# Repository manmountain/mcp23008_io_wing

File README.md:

# MCP23008 io-wing

* IO expander wing for Adafruit Feather boards

Missing IO pins in your feather project? The MCP23008 I2C GPIO expander is great for situations like this. Add another 8 pins to your Feather using a MCP23008 port expander. The MCP23008 uses two i2c pins (these can be shared with other i2c devices), and in exchange gives you 8 general purpose pins. You can set each of 8 pins to be input, output, or input with a pullup. There's even the ability to get an interrupt via an external pin when any of the inputs change so you don't have to keep polling the chip.

You can sink/source up to 20mA from any of the I/O pins so this will work for LEDs and such. You can set the i2c address by tying the ADDR0-2 pins to power or ground by shorting solder jumpers, for up to 8 unique addresses. That means 8 chips can share a single i2c bus - that's 64 I/O pins for your Feather!

## Configure i2c address

This wing uses i2c 7-bit address between 0x20-0x27, selectable with jumpers. On the left side of the wing there is 3 small solder jumpers labeled A0 - A2. By shorting out the solder jumper A0, A1, and A2 you can change the i2c address of the MCP23008.

| A2 | A1 | A0 | Address |
| --- | --- | --- | --- | 
| open | open | open | 0x20 |
| open | open | closed  | 0x21 |
| open | closed | open | 0x22 |
| open | closed | closed | 0x23 |
| closed | open | open | 0x24 |
| closed | open | closed  | 0x25 |
| closed | closed | open | 0x26 |
| closed | closed | closed | 0x27 |

## Using interrupts

To use the interrupt from the MCP23008 short one of the solder jumper on the backside of the wing to connect the interrupt pin from the MCP23008 to the corresponding pin on the Feather.

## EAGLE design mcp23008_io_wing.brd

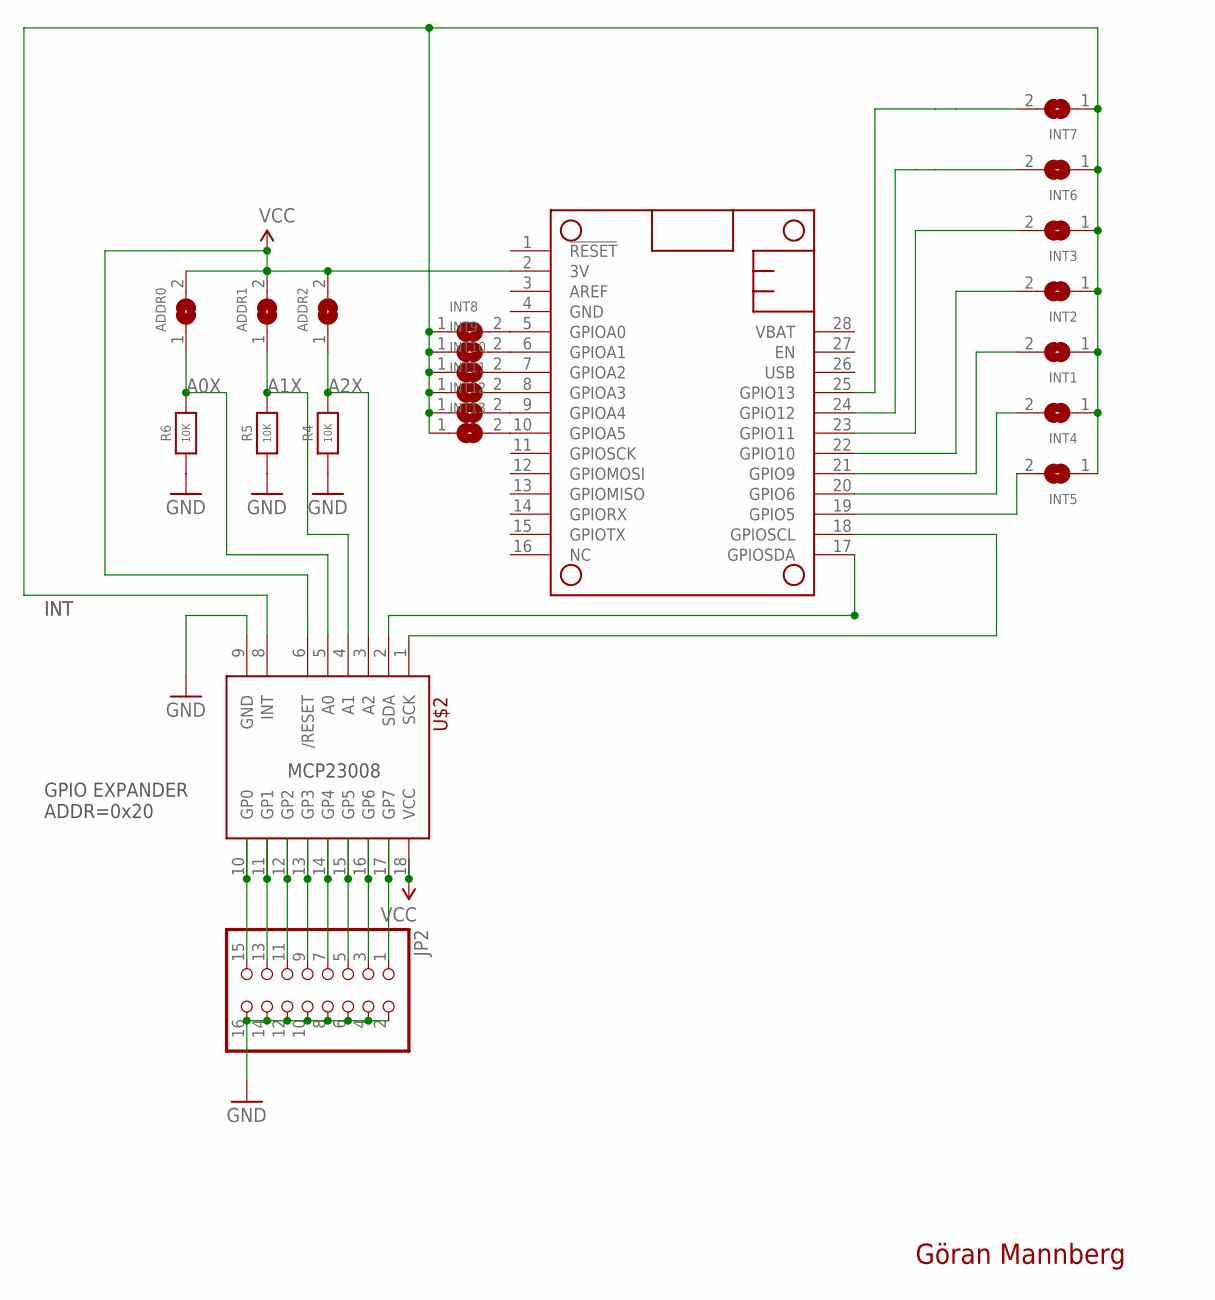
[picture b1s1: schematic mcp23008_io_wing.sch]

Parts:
ADDR0, ADDR1, ADDR2: SOLDERJUMPER; SOLDERJUMPER_ARROW_NOPASTE
INT1, INT2, INT3, INT4, INT5, INT6, INT7, INT8, INT9, INT10, INT11, INT12, INT13: SOLDERJUMPER; SOLDERJUMPER_ARROW_NOPASTE
JP2: HEADER-2X8_SHROUDED; 2X08_SHROUDED
MS1: FEATHERWING
R4, R5, R6: 10K; 0603-NO
U$2: MCP23008; SOIC-18-W-MAXIM

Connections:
3V: ADDR0.2, ADDR1.2, ADDR2.2, MS1.2 (3V), U$2.6 (/RESET), U$2.18 (VCC)
A0X: ADDR0.1, R6.2, U$2.5 (A0)
A1X: ADDR1.1, R5.2, U$2.4 (A1)
A2X: ADDR2.1, R4.2, U$2.3 (A2)
GND: JP2.2, JP2.4, JP2.6, JP2.8, JP2.10, JP2.12, JP2.14, JP2.16, MS1.4 (GND), R4.1, R5.1, R6.1, U$2.9 (GND)
GPA0: JP2.1, U$2.17 (GP7)
GPA1: JP2.3, U$2.16 (GP6)
GPA2: JP2.5, U$2.15 (GP5)
GPA3: JP2.7, U$2.14 (GP4)
GPA4: JP2.9, U$2.13 (GP3)
GPA5: JP2.11, U$2.12 (GP2)
GPA6: JP2.13, U$2.11 (GP1)
GPA7: JP2.15, U$2.10 (GP0)
INT: INT1.1, INT2.1, INT3.1, INT4.1, INT5.1, INT6.1, INT7.1, INT8.1, INT9.1, INT10.1, INT11.1, INT12.1, INT13.1, U$2.8 (INT)
unnamed: INT1.2, MS1.21 (GPIO9)
unnamed: INT2.2, MS1.22 (GPIO10)
unnamed: INT3.2, MS1.23 (GPIO11)
unnamed: INT6.2, MS1.24 (GPIO12)
unnamed: INT7.2, MS1.25 (GPIO13)
unnamed: INT8.2, MS1.5 (GPIOA0)
unnamed: INT5.2, MS1.19 (GPIO5)
unnamed: INT4.2, MS1.20 (GPIO6)
unnamed: INT9.2, MS1.6 (GPIOA1)
unnamed: INT10.2, MS1.7 (GPIOA2)
unnamed: INT11.2, MS1.8 (GPIOA3)
unnamed: INT12.2, MS1.9 (GPIOA4)
unnamed: INT13.2, MS1.10 (GPIOA5)
SCL: MS1.18 (GPIOSCL), U$2.1 (SCK)
SDA: MS1.17 (GPIOSDA), U$2.2 (SDA)

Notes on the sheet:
MCP23008
GPIO EXPANDER ADDR=0x20
Göran Mannberg

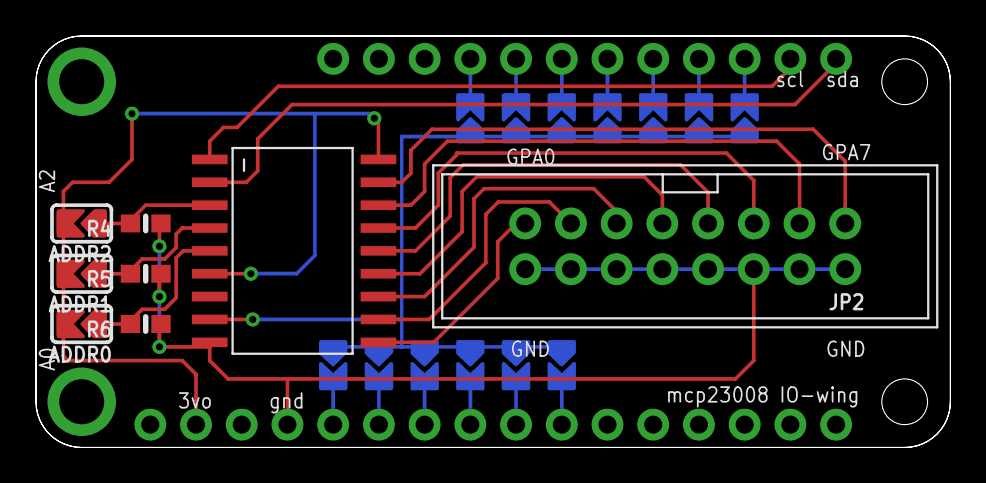
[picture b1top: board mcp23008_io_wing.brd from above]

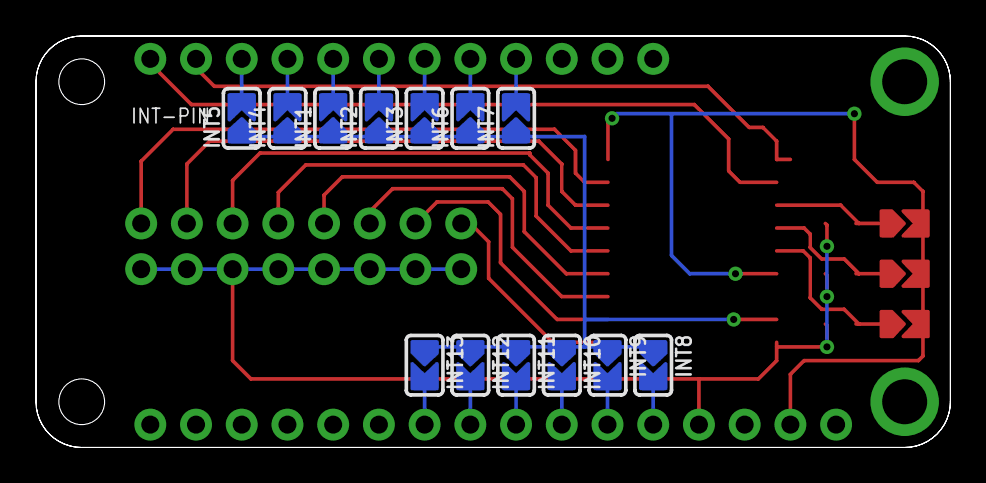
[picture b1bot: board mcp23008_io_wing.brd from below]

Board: 2 copper layers, 50.8 x 22.9 mm, 22 parts (13 on the bottom side), 29 nets.

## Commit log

2020-12-07 fixed bottom soldermask
2020-12-07 added pcb images
2020-12-07 Update README.md
    Updated readme with images and text
2020-12-09 updated board and pcb images
2021-01-07 pcb v2
